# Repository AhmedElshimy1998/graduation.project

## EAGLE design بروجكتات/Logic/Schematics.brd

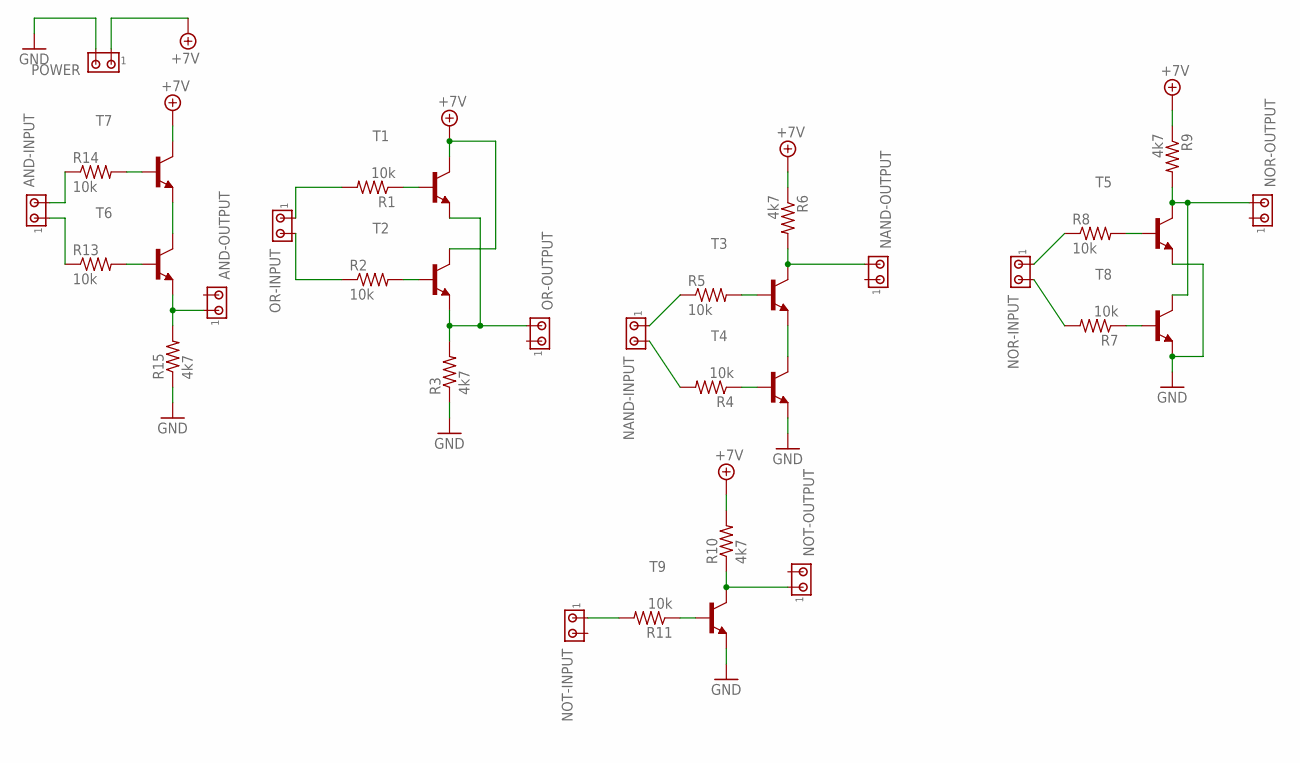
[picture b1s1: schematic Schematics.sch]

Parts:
AND-INPUT: MTA02-100; 10X02MTA
AND-OUTPUT: MTA02-100; 10X02MTA
NAND-INPUT: MTA02-100; 10X02MTA
NAND-OUTPUT: MTA02-100; 10X02MTA
NOR-INPUT: MTA02-100; 10X02MTA
NOR-OUTPUT: MTA02-100; 10X02MTA
NOT-INPUT: MTA02-100; 10X02MTA
NOT-OUTPUT: MTA02-100; 10X02MTA
OR-INPUT: MTA02-100; 10X02MTA
OR-OUTPUT: MTA02-100; 10X02MTA
POWER: MTA02-100; 10X02MTA
R1, R2, R4, R5, R7, R8, R11, R13, R14: 10k; 0309/12
R3, R6, R9, R10, R15: 4k7; 0309/12
T1, T2, T3, T4, T5, T6, T7, T8, T9: -NPN-TO92-EBC; TO92-EBC

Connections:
+7V: POWER.1, R6.1, R9.1, R10.2, T1.C, T2.C, T7.C
GND: POWER.2, R3.1, R15.1, T4.E, T5.E, T8.E, T9.E
unnamed: NAND-OUTPUT.2, R6.2, T3.C
unnamed: T6.C, T7.E
unnamed: R13.2, T6.B
unnamed: R14.2, T7.B
unnamed: AND-INPUT.2, R14.1
unnamed: AND-INPUT.1, R13.1
unnamed: AND-OUTPUT.1, R15.2, T6.E
unnamed: OR-INPUT.1, R1.2
unnamed: OR-INPUT.2, R2.1
unnamed: R2.2, T2.B
unnamed: R1.1, T1.B
unnamed: OR-OUTPUT.2, R3.2, T1.E, T2.E
unnamed: R5.2, T3.B
unnamed: NAND-INPUT.1, R5.1
unnamed: R4.1, T4.B
unnamed: T3.E, T4.C
unnamed: NAND-INPUT.2, R4.2
unnamed: NOR-OUTPUT.2, R9.2, T5.C, T8.C
unnamed: R8.2, T5.B
unnamed: NOR-INPUT.1, R8.1
unnamed: R7.1, T8.B
unnamed: NOT-OUTPUT.1, R10.1, T9.C
unnamed: NOR-INPUT.2, R7.2
unnamed: R11.1, T9.B
unnamed: NOT-INPUT.1, R11.2

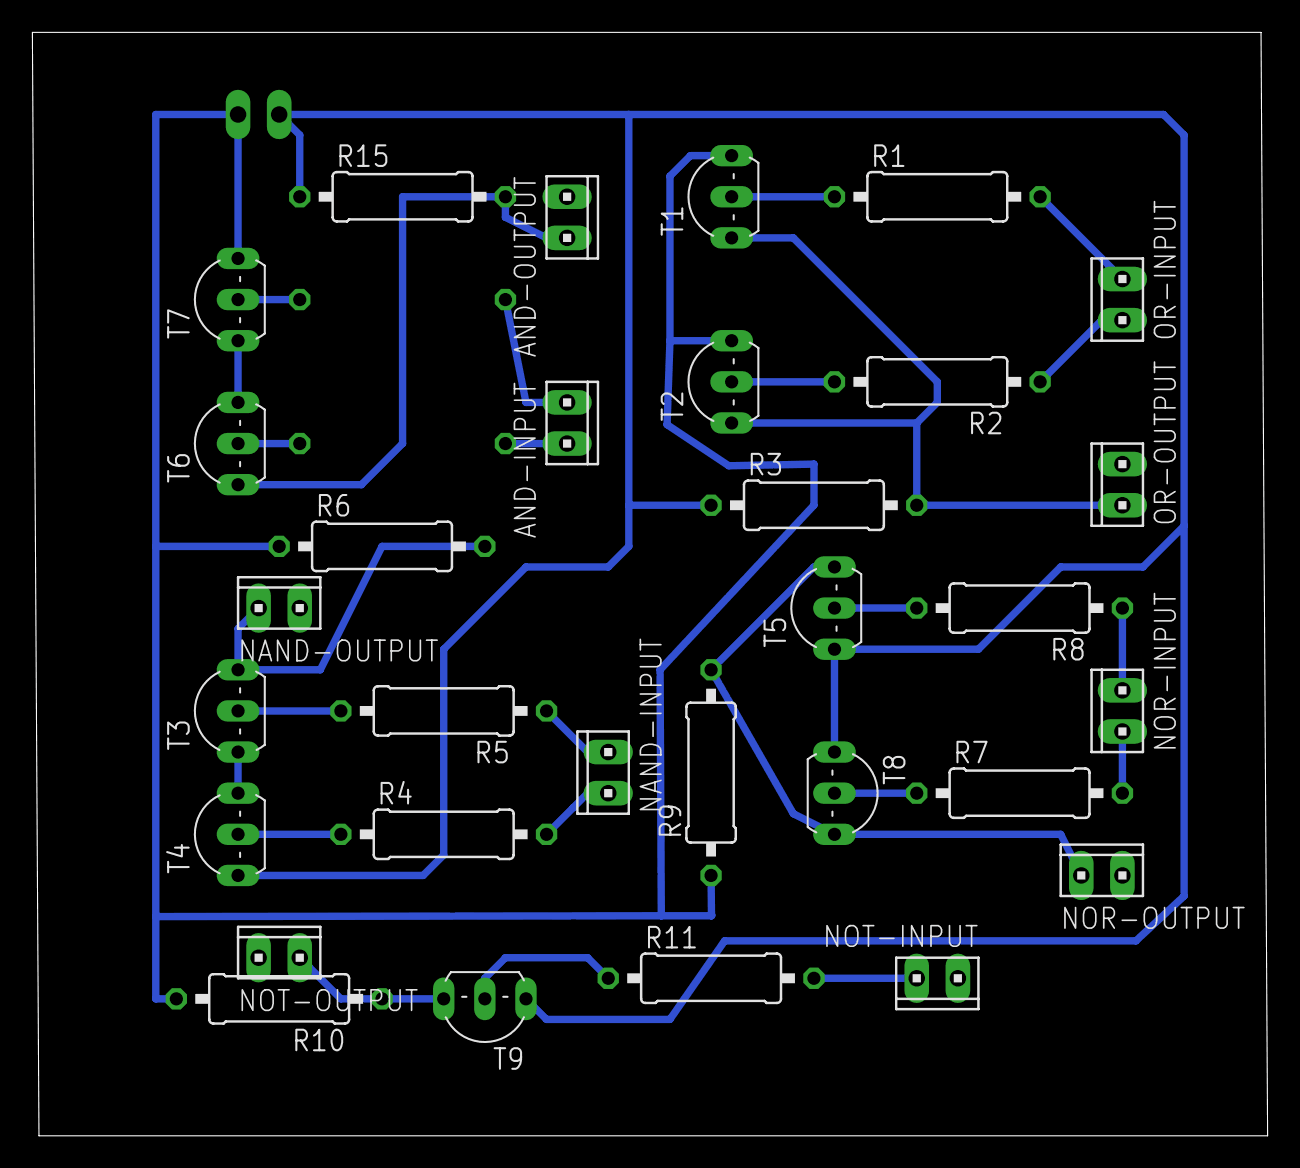
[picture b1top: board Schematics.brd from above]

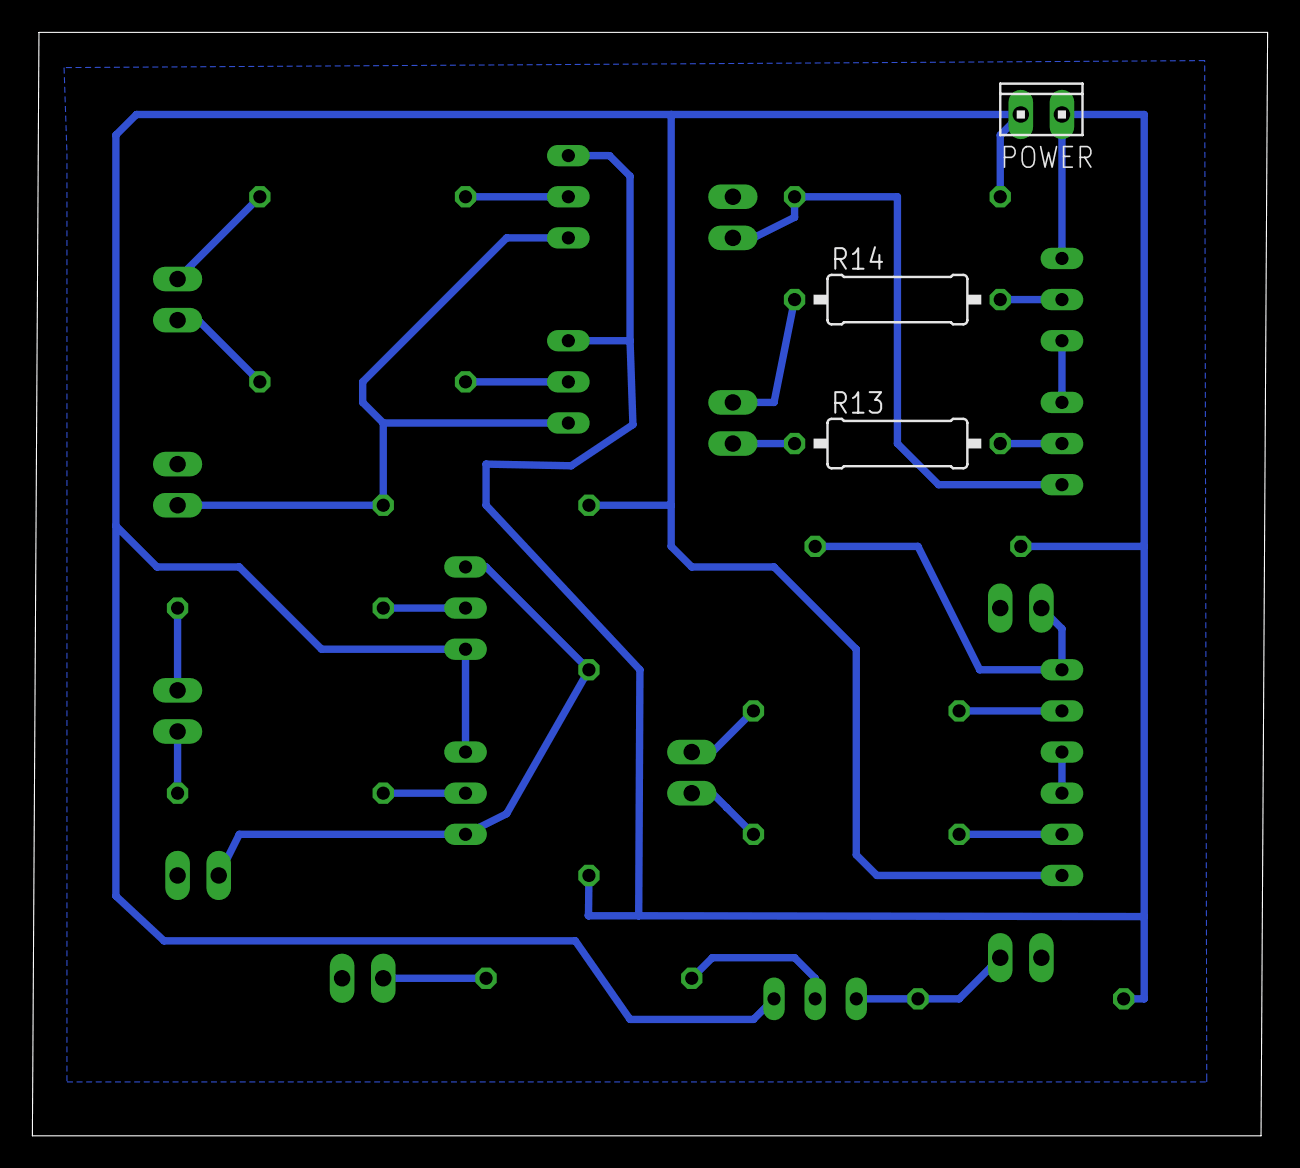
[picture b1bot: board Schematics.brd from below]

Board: 2 copper layers, 76.3 x 68.1 mm, 34 parts (3 on the bottom side), 27 nets.

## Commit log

2018-04-29 my project
    it is my project
